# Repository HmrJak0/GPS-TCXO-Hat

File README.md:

# GPS-TCXO-Hat
More documentation coming soon. 
To be paired with an AML-S905X-CC for FT8/JS8 and other portable, offline, high-accuracy, time-keeping, needs.

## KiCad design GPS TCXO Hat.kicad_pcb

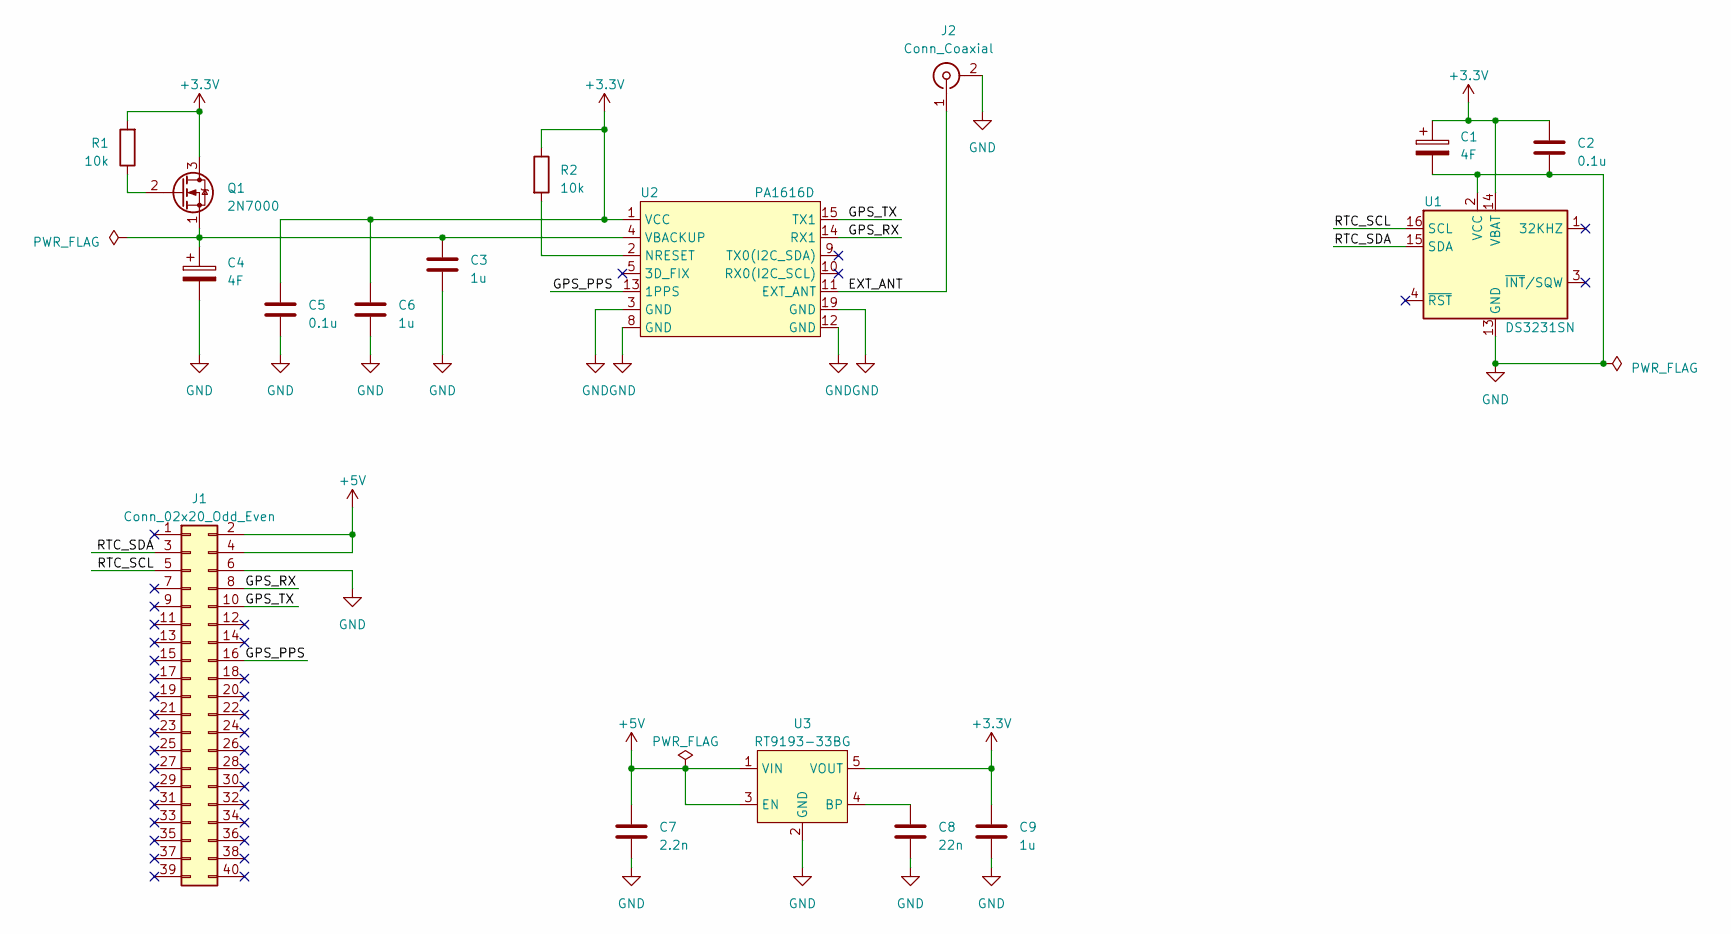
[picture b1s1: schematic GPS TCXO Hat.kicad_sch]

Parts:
C1, C4: 4F; Type-H Supercapacitor
C2, C5: 0.1u; C_1206_3216Metric
C3, C6, C9: 1u; C_1206_3216Metric
C7: 2.2n; C_1206_3216Metric
C8: 22n; C_1206_3216Metric
J1: Conn_02x20_Odd_Even; PinSocket_2x20_P2.54mm_Vertical
J2: Conn_Coaxial; SMA_Amphenol_901-143_Horizontal
Q1: 2N7000; TO-92_Inline
R1, R2: 10k; R_1206_3216Metric
U1: DS3231SN; SOIC-16W_7.5x10.3mm_P1.27mm
U2: PA1616D
U3: RT9193-33BG; SOT-23-5

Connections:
+3.3V: C1.1, C2.1, C5.1, C6.1, C9.1, Q1.3 (D), R1.2, R2.1, U1.14 (VBAT), U2.1 (VCC), U3.5 (VOUT)
+5V: C7.1, J1.2, J1.4, U3.1 (VIN), U3.3 (EN)
/EXT_ANT: J2.1 (In), U2.11 (EXT_ANT)
/GPS_PPS: J1.16, U2.13 (1PPS)
/GPS_RX: J1.8, U2.14 (RX1)
/GPS_TX: J1.10, U2.15 (TX1)
/RTC_SCL: J1.5, U1.16 (SCL)
/RTC_SDA: J1.3, U1.15 (SDA)
GND: C1.2, C2.2, C3.2, C4.2, C5.2, C6.2, C7.2, C8.2, C9.2, J1.6, J2.2 (Ext), U1.2 (VCC), U1.5 (GND), U1.6 (GND), U1.7 (GND), U1.8 (GND), U1.9 (GND), U1.10 (GND), U1.11 (GND), U1.12 (GND), U1.13 (GND), U2.3 (GND), U2.8 (GND), U2.12 (GND), U2.19 (GND), U3.2 (GND)
unnamed: Q1.2 (G), R1.1
unnamed: C3.1, C4.1, Q1.1 (S), U2.4 (VBACKUP)
unnamed: R2.2, U2.2 (NRESET)
unnamed: C8.1, U3.4 (BP)

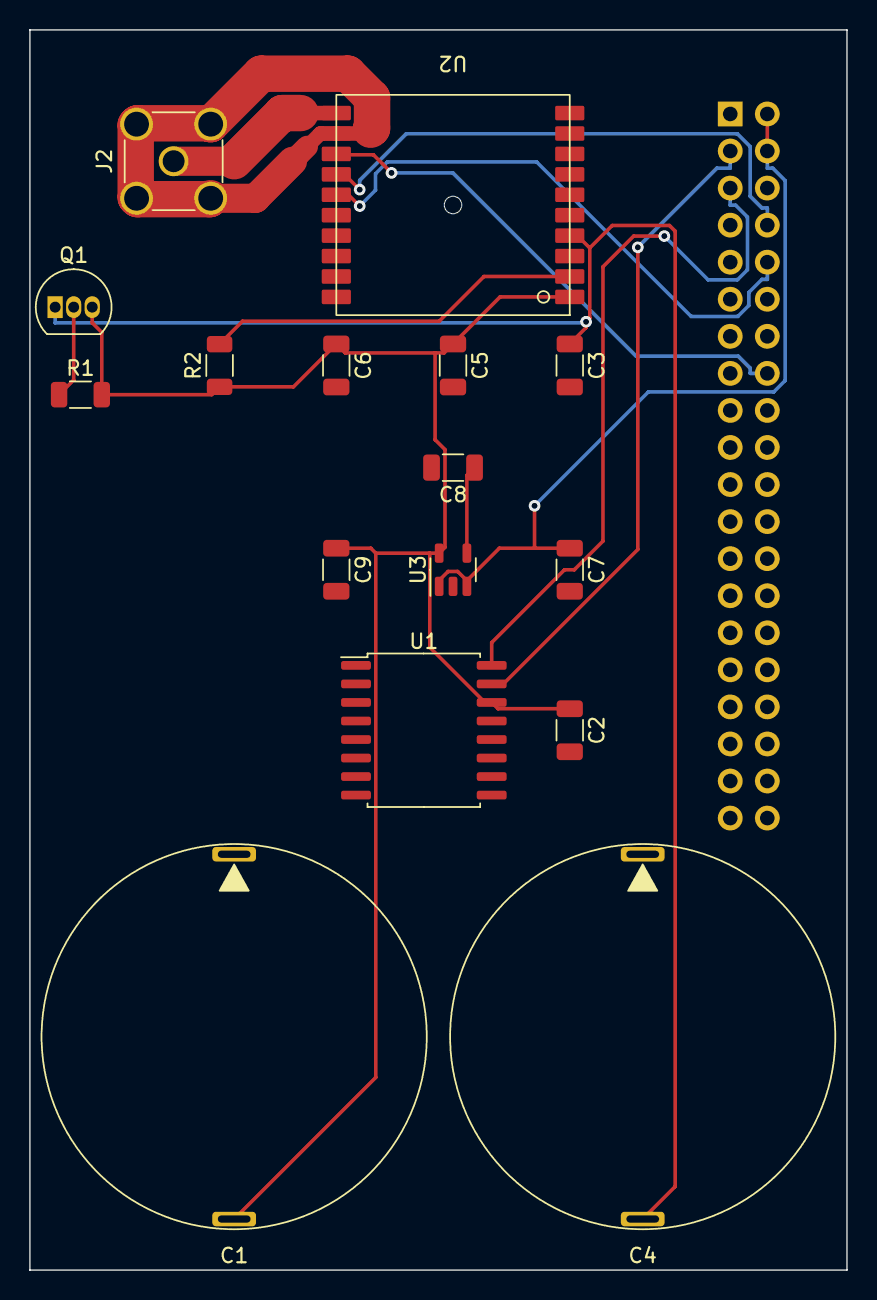
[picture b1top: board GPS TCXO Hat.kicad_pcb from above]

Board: 2 copper layers, 56.0 x 85.0 mm, 17 parts (1 on the bottom side), 13 nets.

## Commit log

2023-02-21 initial file commit
